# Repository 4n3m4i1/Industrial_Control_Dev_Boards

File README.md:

# Industrial_Control_Dev_Boards
For many projects a deeply embeddable development board is needed with the capability to take standard industrial DC voltages (12V, 24V, 36V) as input, and reliably provide outputs to anything else in a control/automation system. There aren't great options that support single side mounting (a la Pi Pico) that provide standard peripherals as well as CAN and possibly LIN, so here are some boards!  
  
## Board Families
- Waffle
The Waffle series is based on the F2800154QXXX (C2000 / dual TMS320C28x core) offerings from TI, which are generally aimed at the automotive market and thus provide good interfacing abilities for most controls needs. Several options are offered in the Waffle family (or rather, will, as my needs change) that only vary in pin count.
  
- Curly
The Curly series is based around the RP2040 we all know and love with an integrated TI TCAN4551-Q1 or MCP25625T-E_ML for SPI -> CAN conversion. These ICs include integrated CAN transceivers as well! Dual RS232 channels are provided from the boards, tied to the hardware UART peripherals.

- Tornado
Waiting on the new TI M0+ parts w CAN to drop... (MSPM0G)  
  
## Software Support
Once a design has been fabricated and verified boilerplate project templates will be included in each board's respective directory. Library files for on-board interfaceable components will be generally provided. Ensure required software is installed to reduce any compatability issues.
  
## Using Boards in Designs
Once a design has been fabricated and verified a footprint and symbol (KiCad 7) will be included in its respective library. These can be used as AIO components in other projects easily.
  
## Board Fabrication
Many PCBA services exist, and all fabrication files used to order a board will be provided in their respective directories. JLC's PCBA is unique in that their parts stock is in-house, which can be a massive bonus or immense drag depending on what you're trying to do. For my smaller scale their methods generally work, as long as parts selection is done to best fit their stock (and optimize for "Basic" parts over "Extended" parts, which incurr a proportionally large fee for small runs), as such certain choices have been made to optimize costs. Given their internal parts sourcing anyone can simply use the files provided, click "Buy", and assembled boards will show up at your house.
  
If a board is of interest, but you don't want to order it yourself, please contact me. If there is enough interest the fixed costs for setup and shipping can be reduced massively per board.

- Waffle Mini v0
Not verified.
  
- Curly Mini v0
All files provided for JLC PCBA, can be effectively one click ordered fully assembled. Approx. $45 for 5 complete boards, 1/2 parts, 1/2 setup fees, board costs are negligible. 2 day shipping to CA approx. $18.

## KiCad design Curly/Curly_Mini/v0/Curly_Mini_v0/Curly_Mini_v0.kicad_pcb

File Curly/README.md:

# Curly
The Curly series is based on the RP2040, which needs no introduction. The simplicity and open nature of the toolchain make this platform ideal in many respects, and the PIO can be leveraged heavily for custom peripheral creation.  
  
[Datasheet/Reference Manual](https://datasheets.raspberrypi.com/rp2040/rp2040-datasheet.pdf)
  
By default a single size of the Curly is offered.
  
## Curly Sizes
- Curly Mini
    - RP2040, 3V3 I/O
    - 44.5mm x 20mm x 1.6mm, 4 layer
    - Single side pinout for vertical mounting in PCB slot
    - 8 GPIO, 4 A2D / GPIO (Total 12) (AREF == 3.3V, not precision ref)
    - External Chip Reset Pin (Active Low)
    - 7V - 48V DC Input Voltage
    - Integrated CAN controller and transceiver (MCP25625T)
    - Integrated 2 channel RS232 converter (MAX3232)
    - NOT breadboard compatible, designed for custom vertical mounting in DIN enclosures
    - Custom 24 pin footprint + symbol provided in library
    - 3 pin Pico/ARM debug and programming interface
    - 3 pin USB 2.0 interface (D+, D-, GND) on header
    - For JLC/LCSC manufacturing the MCP25625T is used as it's more available

## Recommended Software
The `pico-sdk` toolchain should be installed, either via the repository ([pico-sdk](https://github.com/raspberrypi/pico-sdk)), or on Linux systems the clean setup script ([pico_setup.sh](https://github.com/raspberrypi/pico-setup/blob/master/pico_setup.sh)).  
  
## Programming
A standard ARM/Pico 3 pin (SWCLK, SWDIO, GND) JST connector is provided. Using a Pi Pico or other hardware to run picotool / OpenOCD `.elf` files can be loaded into the board, and GDB debugging can be done.
Picotool writeup will come soon...

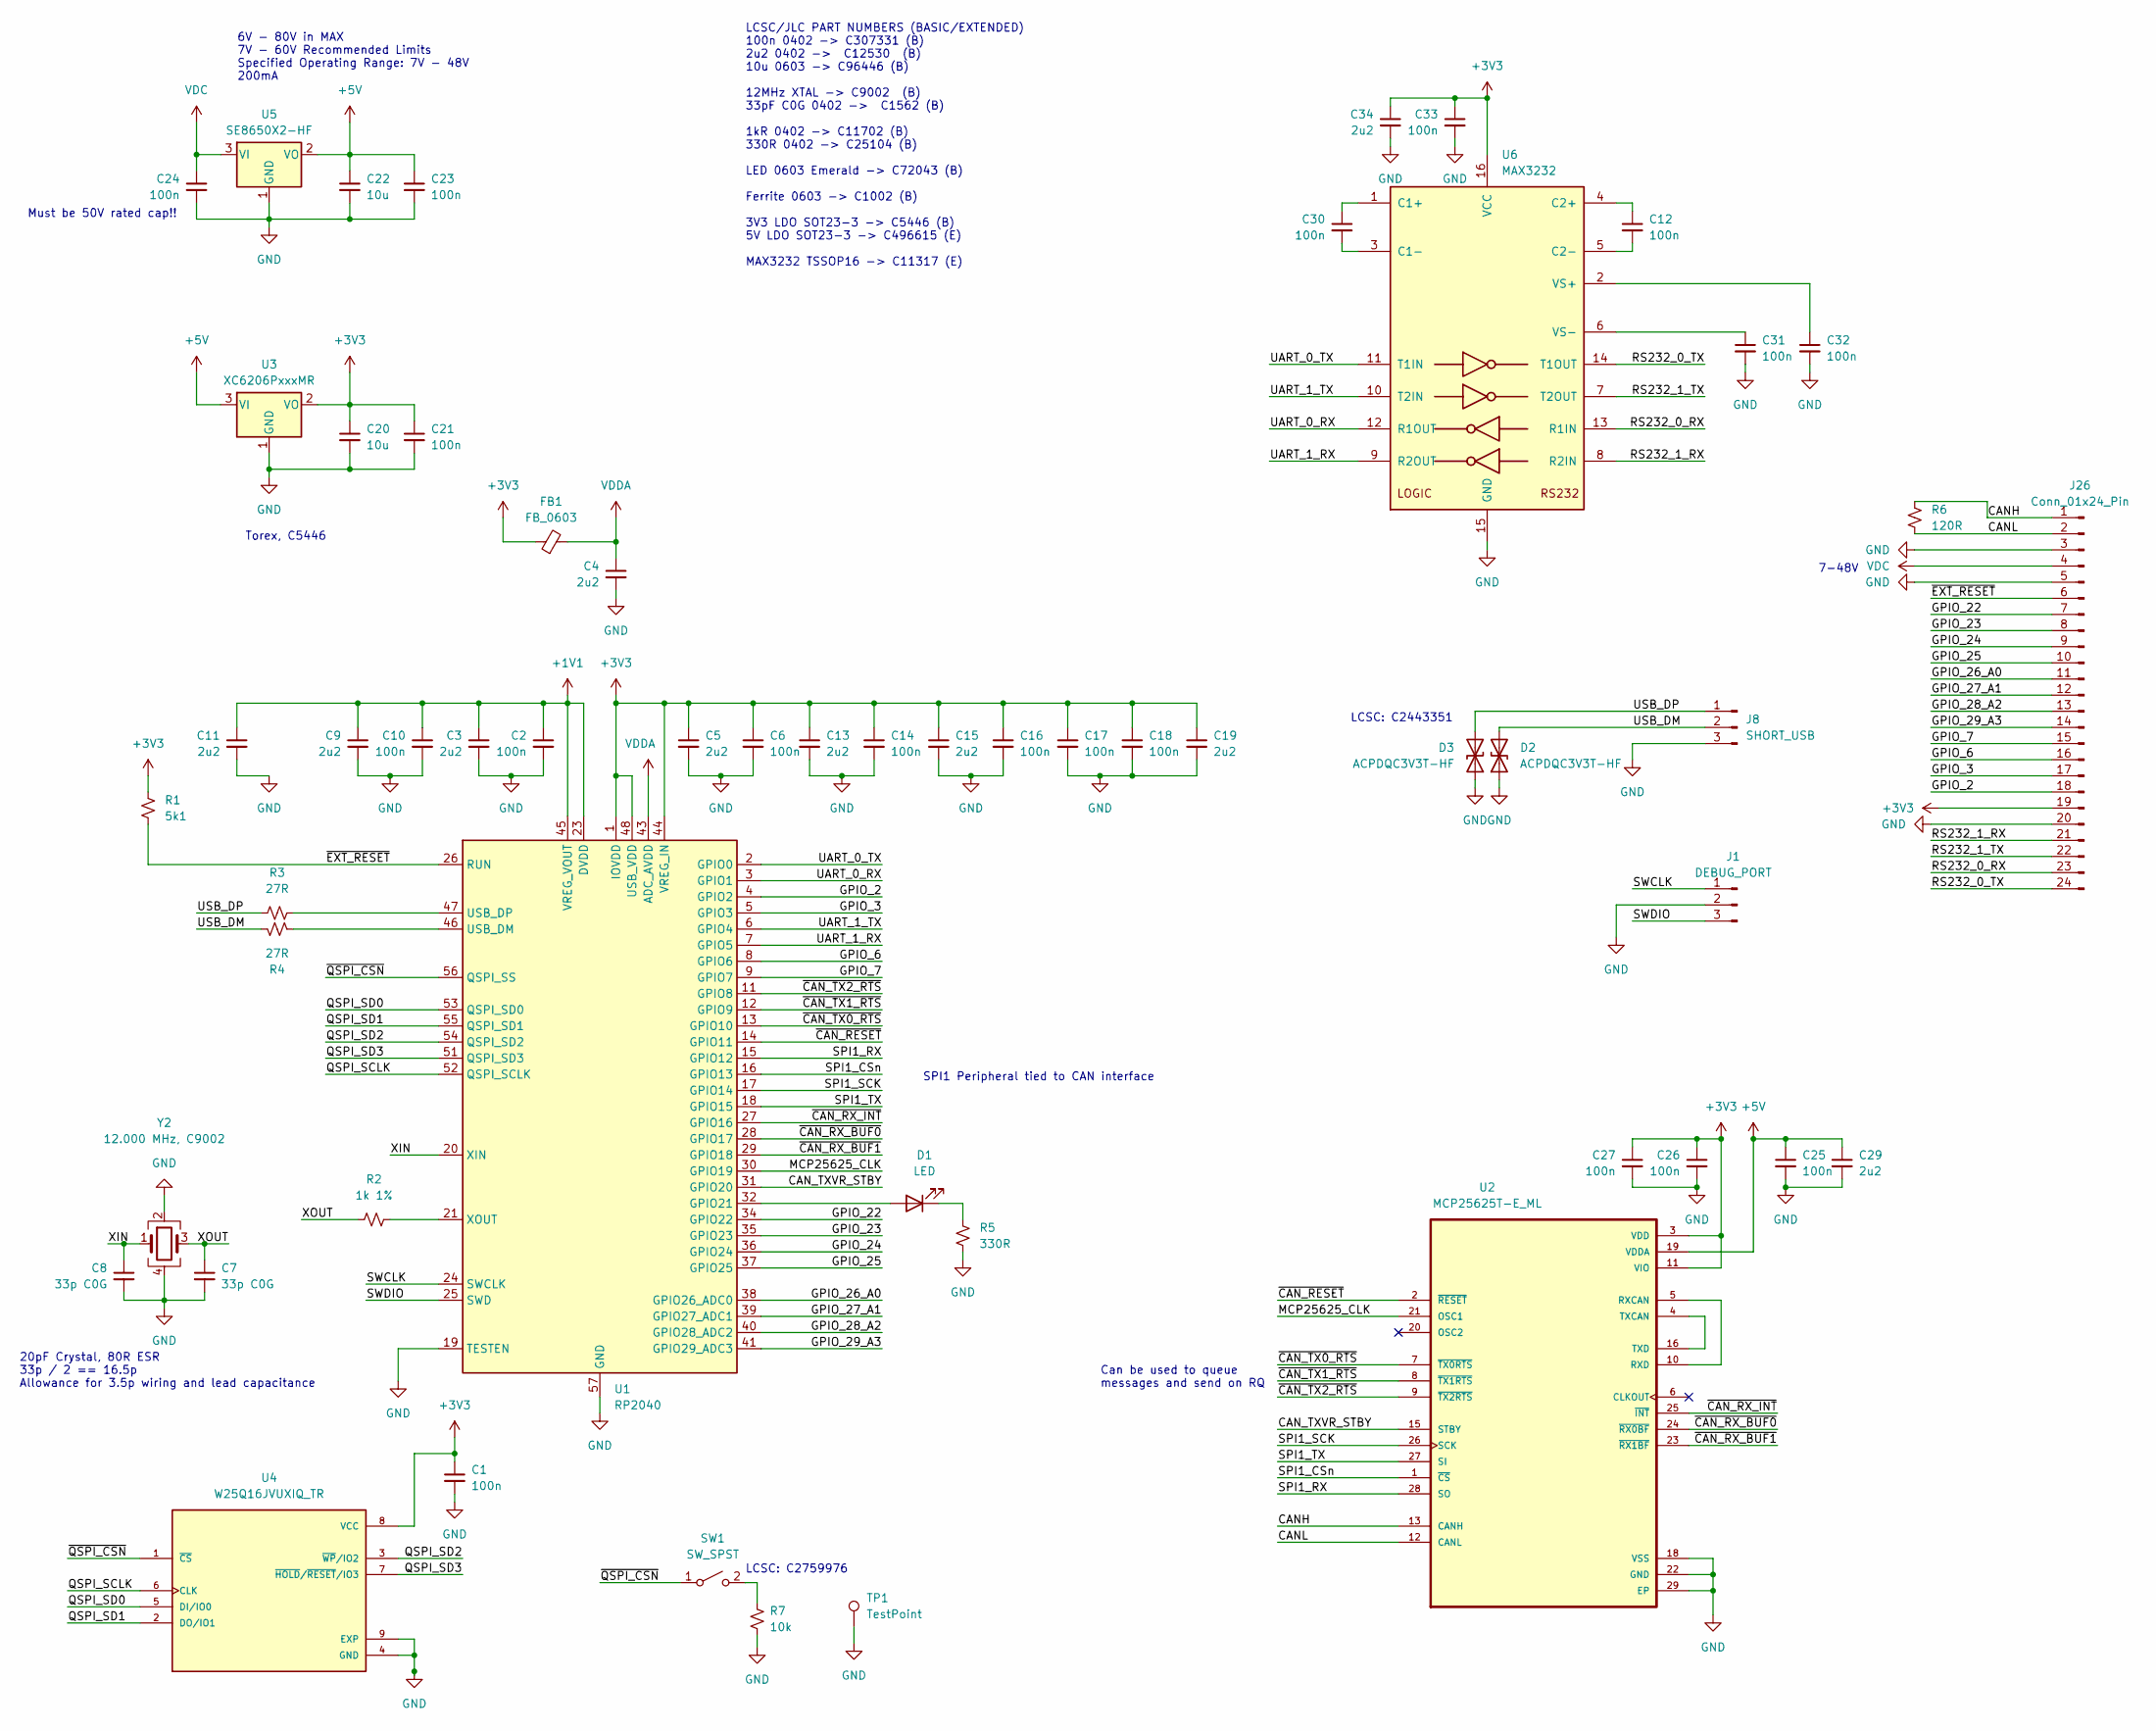
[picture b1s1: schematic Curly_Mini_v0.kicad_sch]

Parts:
C1, C2, C6, C10, C12, C14, C16, C17, C18, C21, C23, C24, C25, C26, C27, C30, C31, C32, C33: 100n; C_0402_1005Metric
C3, C4, C5, C9, C11, C13, C15, C19, C29, C34: 2u2; C_0402_1005Metric
C7, C8: 33p C0G; C_0402_1005Metric
C20, C22: 10u; C_0603_1608Metric
D1: LED; LED_0603_1608Metric
D2, D3: ACPDQC3V3T-HF; 0402C-SOD-923F
FB1: FB_0603; L_0603_1608Metric
J1: DEBUG_PORT; JST_SH_BM03B-SRSS-TB_1x03-1MP_P1.00mm_Vertical
J8: SHORT_USB; PinSocket_1x03_P2.54mm_Vertical
J26: Conn_01x24_Pin; ICDB_Curly_Edge_Conn
R1: 5k1; R_0402_1005Metric
R2: 1k 1%; R_0402_1005Metric
R3, R4: 27R; R_0402_1005Metric
R5: 330R; R_0402_1005Metric
R6: 120R; R_0805_2012Metric_Pad1.20x1.40mm_HandSolder
R7: 10k; R_0402_1005Metric
SW1: SW_SPST; TPS850 J14Q V SMTR LFS
TP1: TestPoint; TestPoint_Pad_D2.0mm
U1: RP2040; QFN-56-1EP_7x7mm_P0.4mm_EP3.2x3.2mm
U2: MCP25625T-E_ML; QFN65P600X600X100-29N; DIGI-KEY_PART_NUMBER MCP25625T-E/MLCT-ND
U3: XC6206PxxxMR; SOT-23-3
U4: W25Q16JVUXIQ_TR; IC_W25Q16JVUXIQ_TR; PARTREV H
U5: SE8650X2-HF; SOT-23-3
U6: MAX3232; TSSOP-16_4.4x5mm_P0.65mm
Y2: 12.000 MHz, C9002; Crystal_SMD_3225-4Pin_3.2x2.5mm

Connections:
+1V1: C2.1, C3.1, C9.1, C10.1, C11.1, U1.23 (DVDD), U1.45 (VREG_VOUT), U1.50 (DVDD)
+3V3: C1.1, C5.1, C6.1, C13.1, C14.1, C15.1, C16.1, C17.1, C18.1, C19.1, C20.1, C21.1, C26.1, C27.1, C33.1, C34.1, FB1.1, J26.19, R1.1, U1.1 (IOVDD), U1.10 (IOVDD), U1.22 (IOVDD), U1.33 (IOVDD), U1.42 (IOVDD), U1.44 (VREG_IN), U1.48 (USB_VDD), U1.49 (IOVDD), U2.3 (VDD), U2.11 (VIO), U3.2 (VO), U4.8 (VCC), U6.16 (VCC)
+5V: C22.1, C23.1, C25.1, C29.1, U2.19 (VDDA), U3.3 (VI), U5.2 (VO)
/CANH: J26.1, R6.1, U2.13 (CANH)
/CANL: J26.2, R6.2, U2.12 (CANL)
/CAN_TXVR_STBY: U1.31 (GPIO20), U2.15 (STBY)
/GPIO_2: J26.18, U1.4 (GPIO2)
/GPIO_3: J26.17, U1.5 (GPIO3)
/GPIO_6: J26.16, U1.8 (GPIO6)
/GPIO_7: J26.15, U1.9 (GPIO7)
/GPIO_22: J26.7, U1.34 (GPIO22)
/GPIO_23: J26.8, U1.35 (GPIO23)
/GPIO_24: J26.9, U1.36 (GPIO24)
/GPIO_25: J26.10, U1.37 (GPIO25)
/GPIO_26_A0: J26.11, U1.38 (GPIO26_ADC0)
/GPIO_27_A1: J26.12, U1.39 (GPIO27_ADC1)
/GPIO_28_A2: J26.13, U1.40 (GPIO28_ADC2)
/GPIO_29_A3: J26.14, U1.41 (GPIO29_ADC3)
/MCP25625_CLK: U1.30 (GPIO19), U2.21 (OSC1)
/QSPI_SCLK: U1.52 (QSPI_SCLK), U4.6 (CLK)
/QSPI_SD0: U1.53 (QSPI_SD0), U4.5 (DI/IO0)
/QSPI_SD1: U1.55 (QSPI_SD1), U4.2 (DO/IO1)
/QSPI_SD2: U1.54 (QSPI_SD2), U4.3 (~WP/IO2)
/QSPI_SD3: U1.51 (QSPI_SD3), U4.7 (~HOLD/~RESET/IO3)
/RS232_0_RX: J26.23, U6.13 (R1IN)
/RS232_0_TX: J26.24, U6.14 (T1OUT)
/RS232_1_RX: J26.21, U6.8 (R2IN)
/RS232_1_TX: J26.22, U6.7 (T2OUT)
/SPI1_CSn: U1.16 (GPIO13), U2.1 (~CS)
/SPI1_RX: U1.15 (GPIO12), U2.28 (SO)
/SPI1_SCK: U1.17 (GPIO14), U2.26 (SCK)
/SPI1_TX: U1.18 (GPIO15), U2.27 (SI)
/SWCLK: J1.1, U1.24 (SWCLK)
/SWDIO: J1.3, U1.25 (SWD)
/UART_0_RX: U1.3 (GPIO1), U6.12 (R1OUT)
/UART_0_TX: U1.2 (GPIO0), U6.11 (T1IN)
/UART_1_RX: U1.7 (GPIO5), U6.9 (R2OUT)
/UART_1_TX: U1.6 (GPIO4), U6.10 (T2IN)
/USB_DM: D2.2 (A2), J8.2, R4.1
/USB_DP: D3.2 (A2), J8.1, R3.1
/XIN: C8.1, U1.20 (XIN), Y2.1
/XOUT: C7.1, R2.1, Y2.3
/~CAN_RESET: U1.14 (GPIO11), U2.2 (~RESET)
/~CAN_RX_BUF0: U1.28 (GPIO17), U2.24 (~RX0BF)
/~CAN_RX_BUF1: U1.29 (GPIO18), U2.23 (~RX1BF)
/~CAN_RX_INT: U1.27 (GPIO16), U2.25 (~INT)
/~CAN_TX0_RTS: U1.13 (GPIO10), U2.7 (~TX0RTS)
/~CAN_TX1_RTS: U1.12 (GPIO9), U2.8 (~TX1RTS)
/~CAN_TX2_RTS: U1.11 (GPIO8), U2.9 (~TX2RTS)
/~EXT_RESET: J26.6, R1.2, U1.26 (RUN)
/~QSPI_CSN: SW1.1 (A), U1.56 (QSPI_SS), U4.1 (~CS)
GND: C1.2, C2.2, C3.2, C4.2, C5.2, C6.2, C7.2, C8.2, C9.2, C10.2, C11.2, C13.2, C14.2, C15.2, C16.2, C17.2, C18.2, C19.2, C20.2, C21.2, C22.2, C23.2, C24.2, C25.2, C26.2, C27.2, C29.2, C31.2, C32.2, C33.2, C34.2, D2.1 (A1), D3.1 (A1), J1.2, J8.3, J26.3, J26.5, J26.20, R5.2, R7.2, TP1.1, U1.19 (TESTEN), U1.57 (GND), U2.18 (VSS), U2.22 (GND), U2.29 (EP), U3.1 (GND), U4.4 (GND), U4.9 (EXP), U5.1 (GND), U6.15 (GND), Y2.2, Y2.4
unnamed: D1.2 (A), U1.32 (GPIO21)
unnamed: D1.1 (K), R5.1
unnamed: R7.1, SW1.2 (B)
unnamed: R4.2, U1.46 (USB_DM)
unnamed: R3.2, U1.47 (USB_DP)
unnamed: R2.2, U1.21 (XOUT)
unnamed: U2.5 (RXCAN), U2.10 (RXD)
unnamed: U2.4 (TXCAN), U2.16 (TXD)
unnamed: C30.1, U6.1 (C1+)
unnamed: C30.2, U6.3 (C1-)
unnamed: C12.1, U6.4 (C2+)
unnamed: C12.2, U6.5 (C2-)
unnamed: C32.1, U6.2 (VS+)
unnamed: C31.1, U6.6 (VS-)
VDC: C24.1, J26.4, U5.3 (VI)
VDDA: C4.1, FB1.2, U1.43 (ADC_AVDD)

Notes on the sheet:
Must be 50V rated cap!!
20pF Crystal, 80R ESR 33p / 2 == 16.5p Allowance for 3.5p wiring and lead capacitance
Torex, C5446
SPI1 Peripheral tied to CAN interface
Can be used to queue messages and send on RQ
LCSC: C2443351
LCSC/JLC PART NUMBERS (BASIC/EXTENDED) 100n 0402 -> C307331 (B) 2u2 0402 -> C12530 (B) 10u 0603 -> C96446 (B) 12MHz XTAL -> C9002 (B) 33pF C0G 0402 -> C1562 (B) 1kR 0402 -> C11702 (B) 330R 0402 -> C25104 (B) LED 0603 Emerald -> C72043 (B) Ferrite 0603 -> C1002 (B) 3V3 LDO SOT23-3 -> C5446 (B) 5V LD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
LCSC: C2759976
6V - 80V in MAX 7V - 60V Recommended Limits Specified Operating Range: 7V - 48V 200mA
7-48V

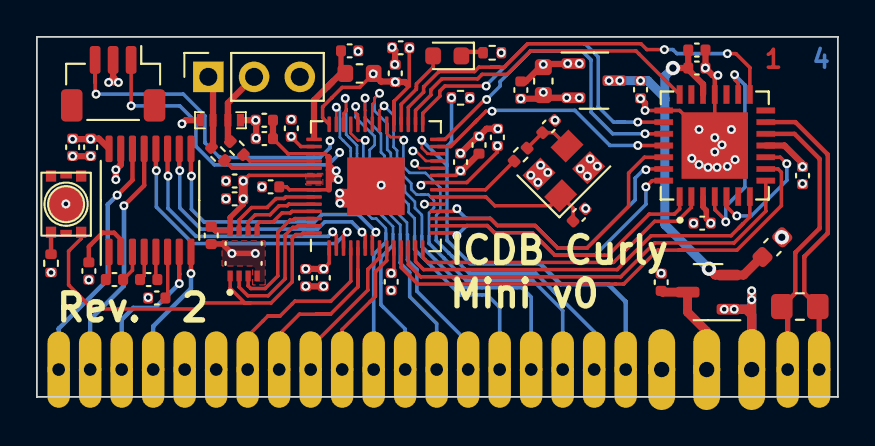
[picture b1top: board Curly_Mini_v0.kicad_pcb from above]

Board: 4 copper layers, 44.5 x 20.0 mm, 56 parts (0 on the bottom side), 68 nets.

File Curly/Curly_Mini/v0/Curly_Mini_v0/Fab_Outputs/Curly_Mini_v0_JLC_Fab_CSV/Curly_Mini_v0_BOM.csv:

Reference,Qty,Value,Footprint,LCSC Part Number
"C1, C2, C6, C10, C12, C14, C16, C17, C18, C21, C23, C24, C25, C26, C27, C30, C31, C32, C33",19,100n,Capacitor_SMD:C_0402_1005Metric,C307331
"C3, C4, C5, C9, C11, C13, C15, C19, C29, C34",10,2u2,Capacitor_SMD:C_0402_1005Metric,C12530
"C7, C8",2,33p C0G,Capacitor_SMD:C_0402_1005Metric,C1562
"C20, C22",2,10u,Capacitor_SMD:C_0603_1608Metric,C96446
D1,1,LED,LED_SMD:LED_0603_1608Metric,C72043
FB1,1,FB_0603,Inductor_SMD:L_0603_1608Metric,C1002
J1,1,DEBUG_PORT,Connector_JST:JST_SH_BM03B-SRSS-TB_1x03-1MP_P1.00mm_Vertical,C160389
R1,1,5k1,Resistor_SMD:R_0402_1005Metric,C25905
R2,1,1k 1%,Resistor_SMD:R_0402_1005Metric,C11702
"R3, R4",2,27R,Resistor_SMD:R_0402_1005Metric,C25092
R5,1,330R,Resistor_SMD:R_0402_1005Metric,C25104
U1,1,RP2040,Package_DFN_QFN:QFN-56-1EP_7x7mm_P0.4mm_EP3.2x3.2mm,C2040
U2,1,MCP25625T-E_ML,ICDB_Curly:QFN65P600X600X100-29N,C191253
U3,1,XC6206PxxxMR,Package_TO_SOT_SMD:SOT-23-3,C5446
U4,1,W25Q16JVUXIQ_TR,ICDB_Curly:IC_W25Q16JVUXIQ_TR,C2843335
U5,1,SE8650X2-HF,Package_TO_SOT_SMD:SOT-23-3,C496615
U6,1,MAX3232,Package_SO:TSSOP-16_4.4x5mm_P0.65mm,C11317
Y2,1,"12.000 MHz,  C9002 ",Crystal:Crystal_SMD_3225-4Pin_3.2x2.5mm,C9002

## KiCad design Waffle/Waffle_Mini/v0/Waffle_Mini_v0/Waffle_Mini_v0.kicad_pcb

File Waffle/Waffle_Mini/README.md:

# Waffle Mini
The Waffle series is based on the F2800154Qxxx family of automotive processors centered around the TMS320C28x processors from TI.
  
The Waffle Mini specifically is based around the F2800154QRHBRQ1 SKU with a minimal amount of GPIO, however for smaller control applications this is acceptable.

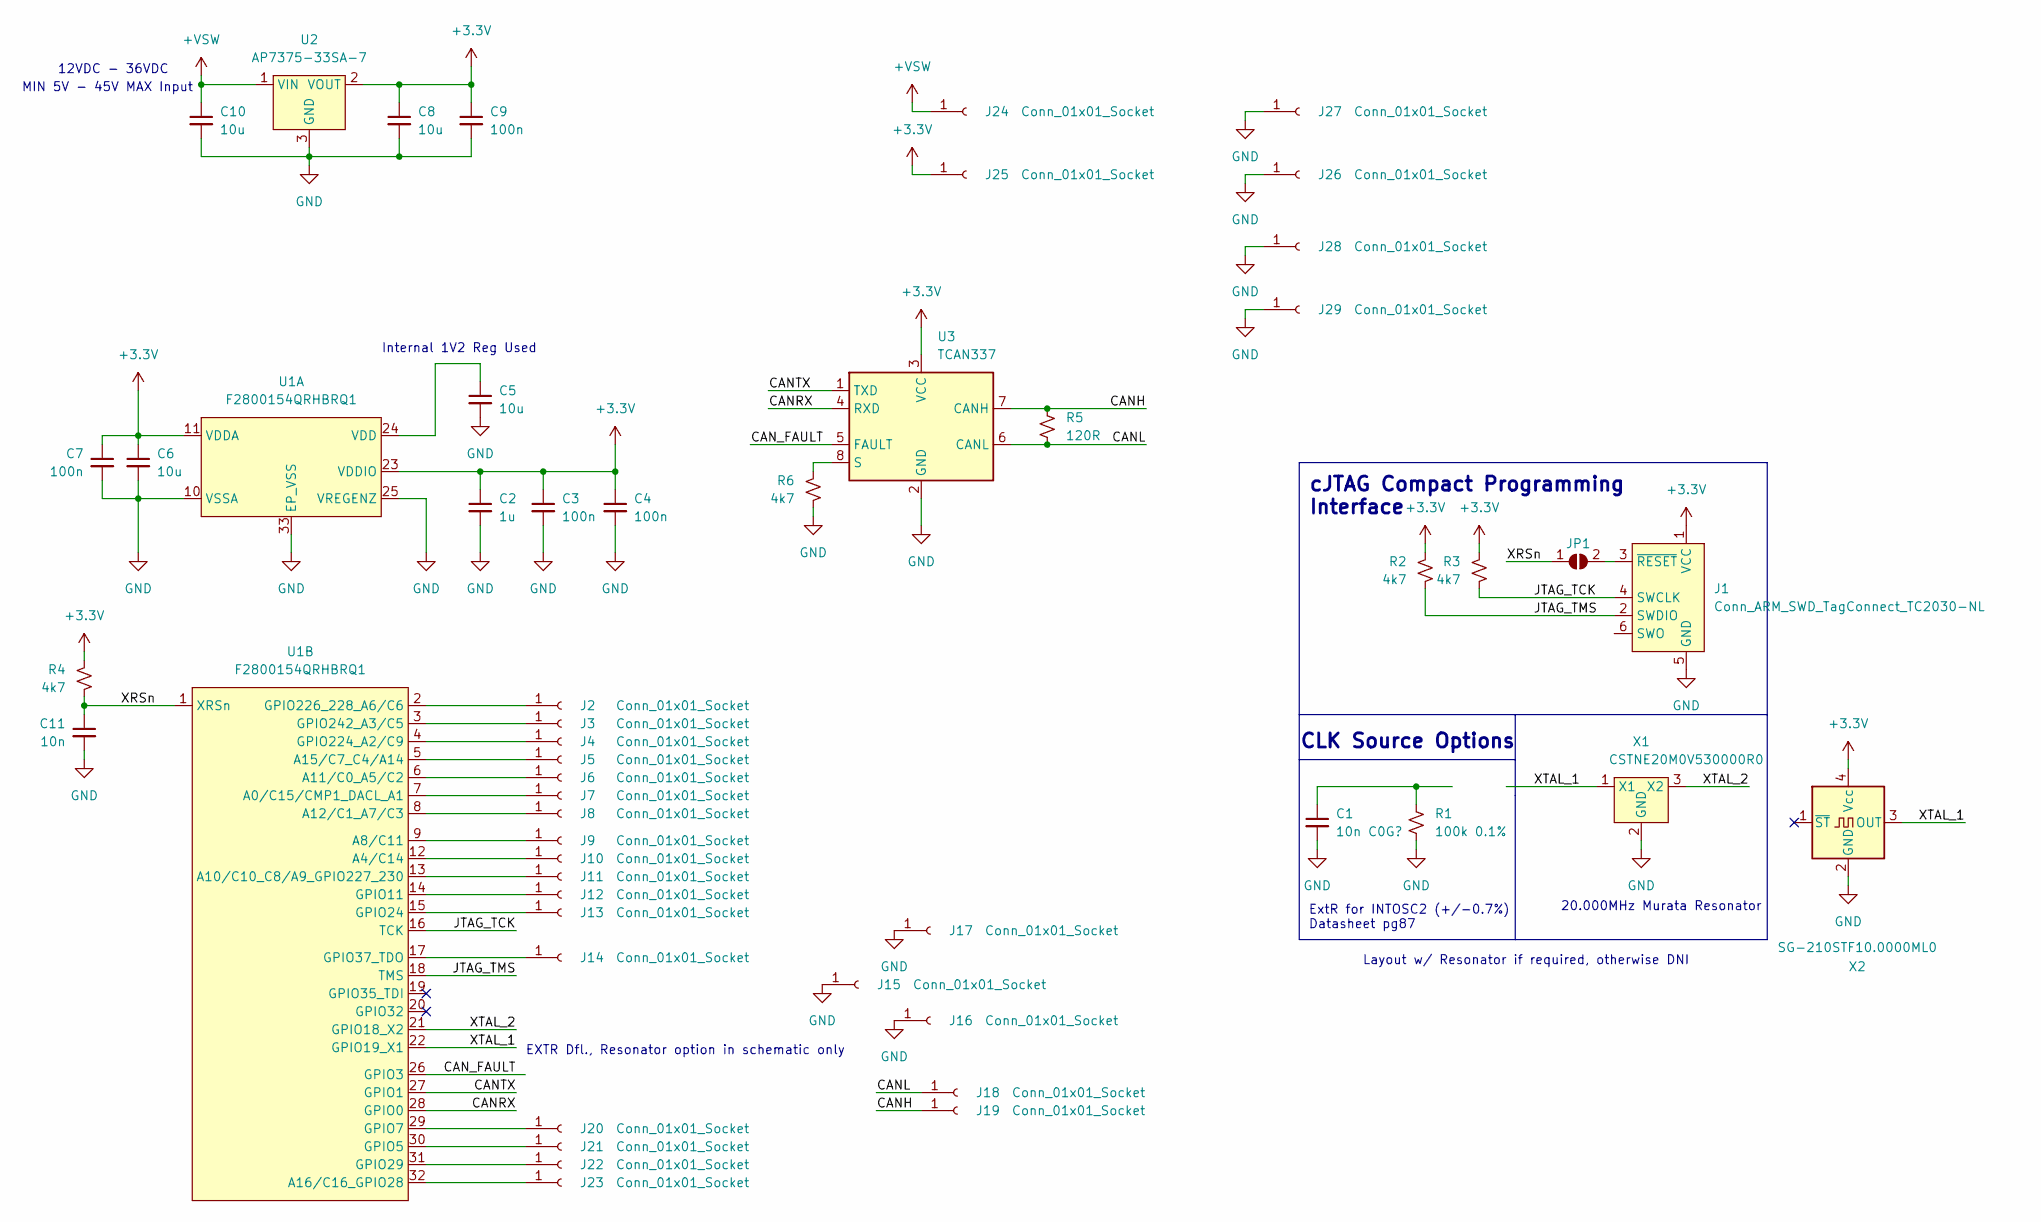
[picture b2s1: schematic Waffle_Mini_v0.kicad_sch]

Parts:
C1: 10n C0G?; C_0603_1608Metric
C2: 1u; C_0805_2012Metric
C3, C4, C7, C9: 100n; C_0603_1608Metric
C5, C6, C8: 10u; C_0805_2012Metric
C10: 10u; C_1210_3225Metric
C11: 10n; C_0603_1608Metric
J1: Conn_ARM_SWD_TagConnect_TC2030-NL; Tag-Connect_TC2030-IDC-NL_2x03_P1.27mm_Vertical
J2, J3, J4, J5, J6, J7, J8, J9, J10, J11, J12, J13, J14, J15, J16, J17, J18, J19, J20, J21, J22, J23, J24, J25, J26, J27, J28, J29: Conn_01x01_Socket; ICDB_Castellated_Pad
JP1: SolderJumper_2_Open; SolderJumper-2_P1.3mm_Open_TrianglePad1.0x1.5mm
R1: 100k 0.1%; R_0603_1608Metric
R2, R3, R4, R6: 4k7; R_0603_1608Metric
R5: 120R; R_0805_2012Metric
U1: F2800154QRHBRQ1; VQFN-32-1EP_5x5mm_P0.5mm_EP3.15x3.15mm
U2: AP7375-33SA-7; SOT-23-3
U3: TCAN337; SOT-23-8
X1: CSTNE20M0V530000R0; CSTNE_Murata_Resonator
X2: SG-210STF10.0000ML0; Oscillator_SMD_SeikoEpson_SG210-4Pin_2.5x2.0mm

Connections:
+3.3V: C2.1, C3.1, C4.1, C6.1, C7.1, C8.1, C9.1, J1.1 (VCC), J25.1, R2.1, R3.1, R4.1, U1.11 (VDDA), U1.23 (VDDIO), U2.2 (VOUT), U3.3 (VCC), X2.4 (Vcc)
+VSW: C10.1, J24.1, U2.1 (VIN)
/CANH: J19.1, R5.1, U3.7 (CANH)
/CANL: J18.1, R5.2, U3.6 (CANL)
/CANRX: U1.28 (GPIO0), U3.4 (RXD)
/CANTX: U1.27 (GPIO1), U3.1 (TXD)
/CAN_FAULT: U1.26 (GPIO3), U3.5 (FAULT)
/JTAG_TCK: J1.4 (SWCLK), R3.2, U1.16 (TCK)
/JTAG_TMS: J1.2 (SWDIO), R2.2, U1.18 (TMS)
/XRSn: C11.1, JP1.1 (A), R4.2, U1.1 (XRSn)
/XTAL_1: U1.22 (GPIO19_X1), X1.1 (X1), X2.3 (OUT)
/XTAL_2: U1.21 (GPIO18_X2), X1.3 (X2)
GND: C1.2, C2.2, C3.2, C4.2, C5.2, C6.2, C7.2, C8.2, C9.2, C10.2, C11.2, J1.5 (GND), J15.1, J16.1, J17.1, J26.1, J27.1, J28.1, J29.1, R1.2, R6.2, U1.10 (VSSA), U1.25 (VREGENZ), U1.33 (EP_VSS), U2.3 (GND), U3.2 (GND), X1.2 (GND), X2.2 (GND)
unnamed: C1.1, R1.1
unnamed: J1.3 (~RESET), JP1.2 (B)
unnamed: J2.1, U1.2 (GPIO226_228_A6/C6)
unnamed: J3.1, U1.3 (GPIO242_A3/C5)
unnamed: J4.1, U1.4 (GPIO224_A2/C9)
unnamed: J5.1, U1.5 (A15/C7_C4/A14)
unnamed: J6.1, U1.6 (A11/C0_A5/C2)
unnamed: J7.1, U1.7 (A0/C15/CMP1_DACL_A1)
unnamed: J8.1, U1.8 (A12/C1_A7/C3)
unnamed: J9.1, U1.9 (A8/C11)
unnamed: J10.1, U1.12 (A4/C14)
unnamed: J11.1, U1.13 (A10/C10_C8/A9_GPIO227_230)
unnamed: J12.1, U1.14 (GPIO11)
unnamed: J13.1, U1.15 (GPIO24)
unnamed: J14.1, U1.17 (GPIO37_TDO)
unnamed: J20.1, U1.29 (GPIO7)
unnamed: J21.1, U1.30 (GPIO5)
unnamed: J22.1, U1.31 (GPIO29)
unnamed: J23.1, U1.32 (A16/C16_GPIO28)
unnamed: C5.1, U1.24 (VDD)
unnamed: R6.1, U3.8 (S)

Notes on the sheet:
ExtR for INTOSC2 (+/-0.7%) Datasheet pg87
EXTR Dfl., Resonator option in schematic only
CLK Source Options
Layout w/ Resonator if required, otherwise DNI
12VDC - 36VDC
Internal 1V2 Reg Used
cJTAG Compact Programming Interface
MIN 5V - 45V MAX Input
20.000MHz Murata Resonator

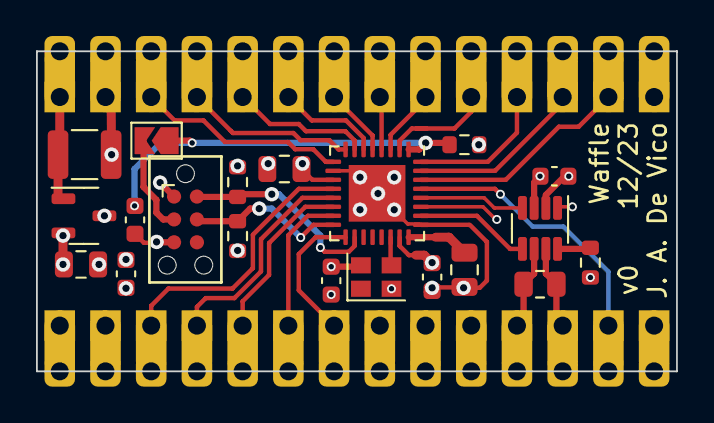
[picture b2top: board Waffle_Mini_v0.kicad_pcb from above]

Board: 4 copper layers, 35.6 x 17.8 mm, 48 parts (0 on the bottom side), 32 nets.

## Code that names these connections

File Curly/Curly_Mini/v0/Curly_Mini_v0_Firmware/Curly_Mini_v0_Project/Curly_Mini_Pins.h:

#ifndef CURLY_MINI_PINS_h
#define CURLY_MINI_PINS_h

// Pin name -> gpio number
enum WAFFLE_MINI_v0_PINS {
    UART0_TX,           // UART0 Hardware Peripheral, tied to MAX3232
    UART0_RX,
    GPIO_2,
    GPIO_3,
    UART1_TX,           // UART1 Hardware Peripheral, tied to MAX3232
    UART1_RX,
    GPIO_6,
    GPIO_7,
    CAN_TX2_RTS,
    CAN_TX1_RTS,
    CAN_TX0_RTS,
    CAN_RESET,
    CAN_SPI_RX,         // SPI1 Hardware Periperal
    CAN_SPI_CS,
    CAN_SPI_SCK,
    CAN_SPI_TX,
    CAN_RX_INT,         // RX ISR Input
    CAN_RX_BUF0,
    CAN_RX_BUF1,
    MCP25625_CLK,       // Clock output to can controller
    CAN_TXVR_STBY,
    BOARD_LED,
    GPIO_22,
    GPIO_23,
    GPIO_24,
    GPIO_25,
    GPIO_26_A0,
    GPIO_27_A1,
    GPIO_28_A2,
    GPIO_29_A3
};

#define SPI_CAN     spi1
#define DFL_CANBAUD (500 * 1000)

#endif

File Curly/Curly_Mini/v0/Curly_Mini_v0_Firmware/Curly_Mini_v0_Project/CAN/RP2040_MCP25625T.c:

#include "RP2040_MCP25625T.h"
// pico-sdk
#include "pico/stdlib.h"
#include "hardware/pwm.h"
#include "hardware/spi.h"



void MCP25625_Setup(spi_inst_t *spi, uint sck_pin, uint cs_pin, uint spi_rx, uint spi_tx, uint can_baud, uint can_clk_pin){
    spi_init(spi, MCP25625_SPI_HZ);     // 10MHz
    
    gpio_init(cs_pin);
    gpio_set_dir(cs_pin, GPIO_OUT);
    gpio_pull_up(cs_pin);               // Pullup just in case
    gpio_put(cs_pin, true);                // CS is active low

    gpio_set_function(sck_pin, GPIO_FUNC_SPI);
    gpio_set_function(spi_rx, GPIO_FUNC_SPI);
    gpio_set_function(spi_tx, GPIO_FUNC_SPI);

    spi_get_hw(spi)->SSPCR0 &= ~(0x000F);   // Clear data width
    spi_get_hw(spi)->SSPCR0 |= 0x0007;      // set to 8 bit txfr widths

    // Setup other CAN GPIO stuff for ISRs and external reset.
    //  Much of this functionality can be done with the SPI interface,
    //      and will be removed in future revisions
#ifdef CURLY_MINI_v0
    gpio_init(CAN_RESET);
    gpio_set_dir(CAN_RESET, GPIO_OUT);
    gpio_put(CAN_RESET, true);

    gpio_init(CAN_TX2_RTS);
    gpio_set_dir(CAN_TX2_RTS, GPIO_OUT);
    gpio_put(CAN_TX2_RTS, true);
    gpio_init(CAN_TX1_RTS);
    gpio_set_dir(CAN_TX1_RTS, GPIO_OUT);
    gpio_put(CAN_TX1_RTS, true);
    gpio_init(CAN_TX0_RTS);
    gpio_set_dir(CAN_TX0_RTS, GPIO_OUT);
    gpio_put(CAN_TX0_RTS, true);

    gpio_init(CAN_RX_INT);
    gpio_set_dir(CAN_RX_INT, GPIO_IN);
    gpio_pull_up(CAN_RX_INT);

    gpio_init(CAN_RX_BUF0);
    gpio_set_dir(CAN_RX_BUF0, GPIO_IN);
    gpio_pull_up(CAN_RX_BUF0);

    gpio_init(CAN_RX_BUF1);
    gpio_set_dir(CAN_RX_BUF1, GPIO_IN);
    gpio_pull_up(CAN_RX_BUF1);
#endif
    gpio_put(CAN_RESET, false);

    gpio_init(can_clk_pin);
    gpio_set_dir(can_clk_pin, GPIO_OUT);
    // Setup CAN Clk @ 20MHz
    //  RP2040 base clock assumed to be 125MHz
    //  125M / 20M = 6.25
    //      Int = 6
    //      Frac is 4 bit fixed pt: .5, .25, .125, .0625
    //      Frac = 1 << 2
    // BUT divide by 2 since we need to run PWM, so:
    //      Int = 3
    //      Frac = .125 = (1 << 1)
    gpio_set_function(can_clk_pin, GPIO_FUNC_PWM);
    uint sliceno = pwm_gpio_to_slice_num(can_clk_pin);
    uint pwmchan = pwm_gpio_to_channel(can_clk_pin);
    pwm_set_chan_level(sliceno, pwmchan, 1);
    pwm_set_wrap(sliceno, 2);
    pwm_set_clkdiv_int_frac(sliceno, 3, (1 << 1));
    pwm_set_enabled(sliceno, true);

    // Finish boot reset
    gpio_put(CAN_RESET, true);

    // Now we need to setup the CAN bit clock... ew
}

// spi_write_read_blocking(spi_inst_t *spi, const uint8_t *src, uint8_t *dst, size_t len)
uint8_t MCP25625_Read_Blocking(spi_inst_t *spi ,uint8_t address){
    uint8_t tval[3]; 
    tval[0] = CAN_CTRL_READ; 
    tval[1] = address;
    uint8_t rval[3];
    spi_write_read_blocking(spi, tval, rval, sizeof(tval));
    return rval[2];
}

void MCP25625_CAN_Message_2_Raw_Arr(uint8_t *arr, struct CAN_Message *msg){
    if(msg && arr){
        arr[XBnDLC] = (msg->len & 0x0F);   // Set len
        arr[XBnSIDH] = ((msg->id >> 3) & 0x0F);
        arr[XBnSIDL] = ((msg->id & 0x07) << 5);
        if(msg->flags.ext){
            arr[XBnSIDL] |= (1 << 3);   // set extended
            arr[XBnSIDL] |= ((msg->id >> (16 + STDIDLEN)) & 0x03);
            arr[XBnEID8] =  (msg->id >> (8 + STDIDLEN));
            arr[XBnEID0] =  (msg->id >> (0 + STDIDLEN));
            arr[XBnDLC]  |= ((msg->flags.ext) ? (1 << 6) : 0);  // ext rtr
        } else {
            arr[XBnSIDL] |= (((msg->flags.remote) ? 1 : 0) << 4);
        }

        for(int n = 0; n < msg->len; ++n) arr[XBnD0 + n] = msg->data[n];
    }
}

void MCP25625_Raw_Arr_2_CAN_Message(struct CAN_Message *msg, uint8_t *arr){
    if(msg && arr){
        msg->id = (arr[XBnSIDL] >> 5) | arr[XBnSIDH];
        msg->flags.ext = arr[XBnSIDL] & (1 << 3);
        if(msg->flags.ext){
            msg->id |= (arr[XBnSIDL] & 0x03) << (16 + STDIDLEN);
            msg->id |= (arr[XBnEID8] << (8 + STDIDLEN));
            msg->id |= (arr[XBnEID0] << (0 + STDIDLEN));

            msg->flags.remote = arr[XBnDLC] & (1 << 6);
        } else {
            msg->flags.remote = arr[XBnSIDL] & (1 << 4);
        }

        msg->len = (arr[XBnDLC] & 0xF);

        for(int n = 0; n < msg->len; ++n) msg->data[n] = arr[XBnD0 + n]; 
    }
}

uint8_t MCP25625_Read_RX_Buffer_Blocking(spi_inst_t *spi, struct CAN_Message *msg, uint8_t buff_num){
    uint8_t tval[13]; 
    tval[0] = CAN_READ_RX_BUFF | buff_num; 
    uint8_t rval[13];
    // Starting transfer from top of RXBxSIDH -> 13 bytes total read
    //  Starting transfer from top of data field -> 8 bytes total read
    //  13 - 8 = 5
    if(buff_num & 0x01){    // Full read
        spi_write_read_blocking(spi, tval, rval, sizeof(tval));
        MCP25625_Raw_Arr_2_CAN_Message(msg, rval);
    } else {                // Just Data Read
        spi_write_read_blocking(spi, tval, rval, sizeof(tval) - MCP_MAILBOX_D0_OFFSET);
        for(int n = 0; n < 8; ++n) msg->data[n] = rval[n];
    }
    
    
    return rval[1];
}

// int spi_write_blocking(spi_inst_t *spi, const uint8_t *src, size_t len);
void MCP25625_Write_Blocking(spi_inst_t *spi, uint8_t address, uint8_t data){
    uint8_t tval[3];
    tval[0] = CAN_CTRL_WRITE;
    tval[1] = address;
    tval[2] = data;
    spi_write_blocking(spi, tval, sizeof(tval));
}

void MCP25625_Write_TX_Buffer_Blocking(spi_inst_t *spi, uint8_t buff_num, uint8_t data){
    uint8_t tval[2];
    tval[0] = CAN_LOAD_TX_BUFF | buff_num;
    tval[1] = data;
    spi_write_blocking(spi, tval, sizeof(tval));
}

void MCP25625_RTS_Blocking(spi_inst_t *spi, uint8_t buff_num){
    uint8_t tval = CAN_CTRL_RTS | buff_num;
    spi_write_blocking(spi, tval, sizeof(tval));
}

void MCP25625_Bit_Modify_Blocking(spi_inst_t *spi, uint8_t addr, uint8_t mask, uint8_t data){
    uint8_t tval[4];
    tval[0] = CAN_CTRL_WRITE;
    tval[1] = addr;
    tval[2] = mask;
    tval[3] = data;
    spi_write_blocking(spi, tval, sizeof(tval));
}

uint8_t MCP25625_Read_Status_Blocking(spi_inst_t *spi){
    uint8_t tval[3]; 
    tval[0] = CAN_READ_STATUS; 
    uint8_t rval[3];
    spi_write_read_blocking(spi, tval, rval, sizeof(tval));
    return rval[2]; // bytes [1] and [2] are the same
}

uint8_t MCP25625_Read_RX_Buff_Status_Blocking(spi_inst_t *spi){
    uint8_t tval[3]; 
    tval[0] = CAN_RX_BUFF_STATUS; 
    uint8_t rval[3];
    spi_write_read_blocking(spi, tval, rval, sizeof(tval));
    return rval[2]; // bytes [1] and [2] are the same
}

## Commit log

2023-12-28 Waffle Mini file dump
2023-12-28 Layout kinda done v0 waffle mini
2023-12-31 Curly added :)
2023-12-31 Curly partially done
2024-01-01 Curly Mini almost done :)
2024-01-01 Curly Mini almost done (again) :)
2024-01-01 Curly Mini RS232 completed
2024-01-01 Curly Mini Prelim layout done
2024-01-02 Final v0 revision made, JLC fab files provided. Castellated holes are ultra expensive, moved to 2 sided edge connect
2024-01-02 R E A D M E E
2024-01-03 Some boilerplate, Curly CAN controller library partial, etc..
2024-01-13 Blinky works on Curly :) Added CAN transceiver to Waffle
2024-01-13 Added USB ESD Protection, USB Boot button - Curly
2024-01-13 Small cleanup on Curly
2024-01-19 Restructured software
2024-11-23 resync
